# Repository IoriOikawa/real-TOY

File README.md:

# realTOY

> Hardware Implementation for the TOY computer from Princeton.

## Architecture

## Verification

1. Install [Verilator](https://github.com/verilator/verilator), the fastest Verilog/SystemVerilog simulator:

   ```bash
   sudo pacman -S verilator
   ```

1. Install JDK, version doesn't matter that much:

   ```bash
   sudo pacman -S jdk-openjdk
   ```

1. Run all test cases:

   ```bash
   make test
   ```

## Hardware Implementation

TODO

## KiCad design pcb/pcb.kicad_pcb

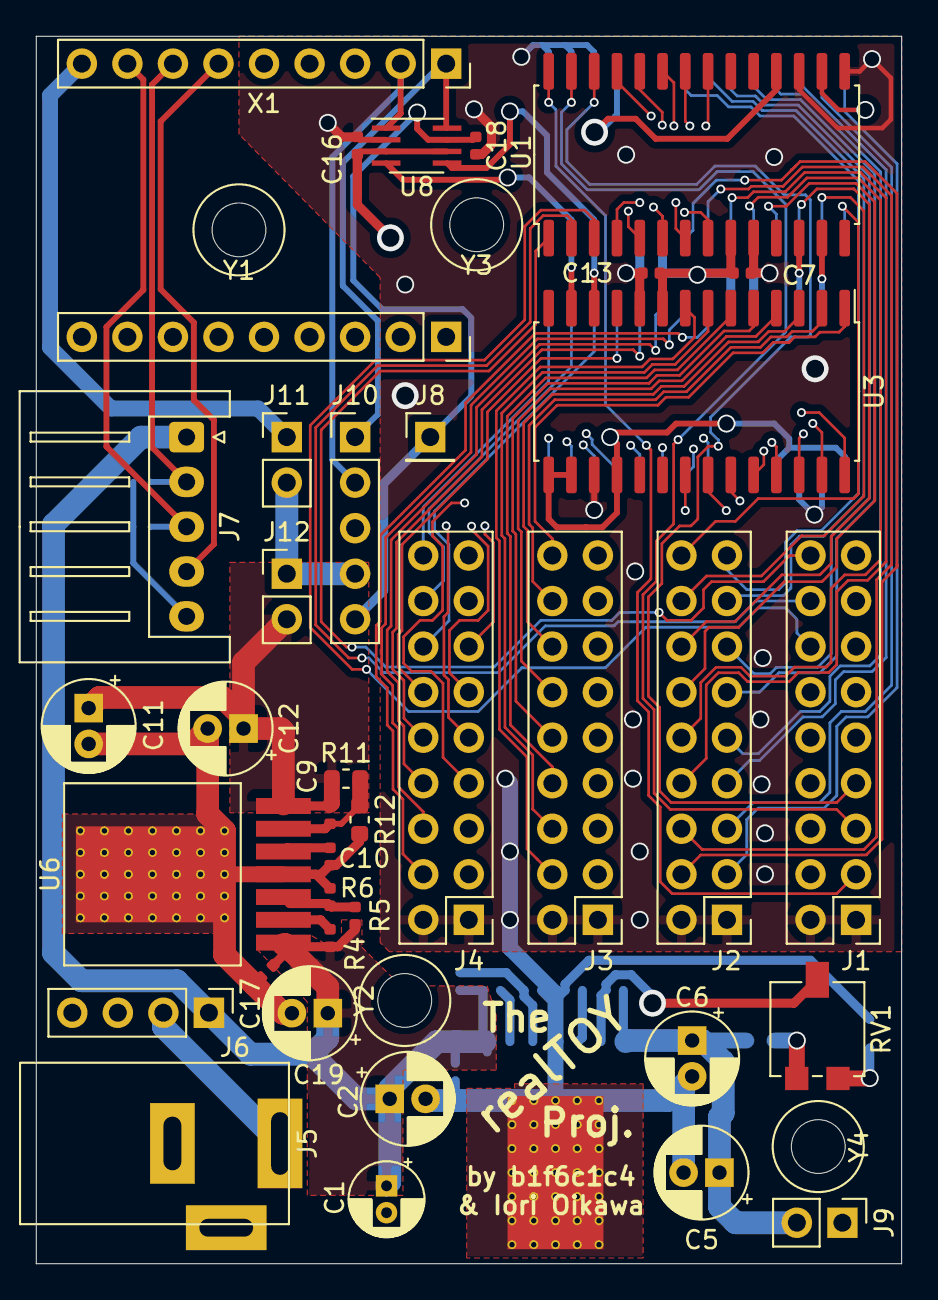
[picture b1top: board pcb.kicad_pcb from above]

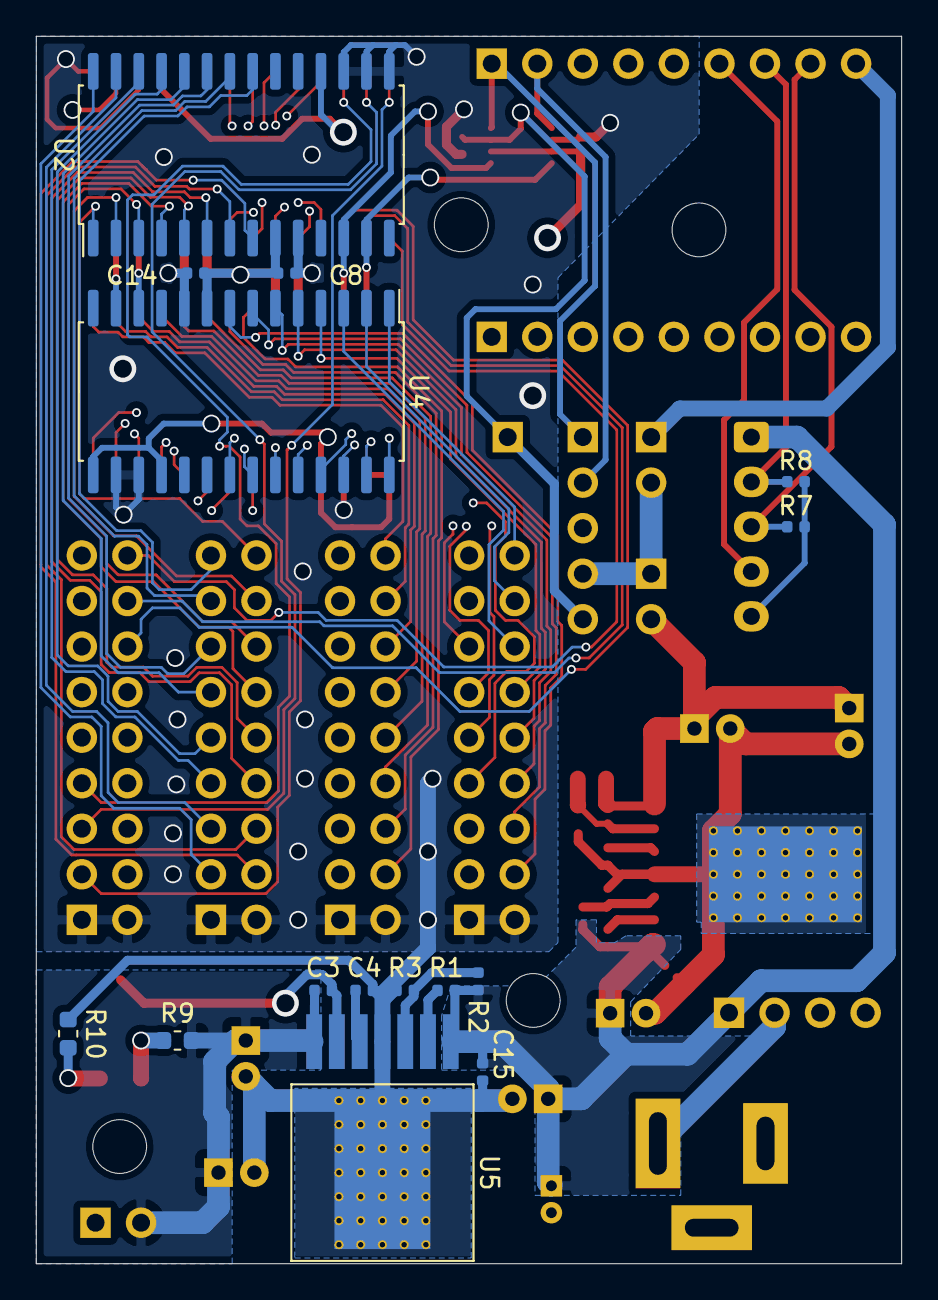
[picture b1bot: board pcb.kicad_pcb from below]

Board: 4 copper layers, 48.3 x 68.5 mm, 56 parts (15 on the bottom side), 90 nets.

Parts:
C1: 22u; CP_Radial_D4.0mm_P1.50mm
C2, C6, C12, C19: 1u; CP_Radial_D5.0mm_P2.00mm
C3, C4, C9, C10: 22n; C_0402_1005Metric
C5, C11: 100u; CP_Radial_D5.0mm_P2.00mm
C7, C8, C13, C14, C15, C16, C17, C18: 100n; C_0402_1005Metric
J1, J2, J3, J4: Conn_02x09_Odd_Even; PinHeader_2x09_P2.54mm_Vertical
J5: Jack-DC; KLDX-0202
J6: Conn_01x04; PinHeader_1x04_P2.54mm_Vertical
J7: Conn_01x05; JST_XH_S5B-XH-A_1x05_P2.50mm_Horizontal
J8: Conn_01x01; PinHeader_1x01_P2.54mm_Vertical
J9, J11, J12: Conn_01x02; PinHeader_1x02_P2.54mm_Vertical
J10: Conn_01x05; PinHeader_1x05_P2.54mm_Vertical
R1, R2, R4, R5, R7, R8: 33k; R_0402_1005Metric
R3, R6: 12k; R_0402_1005Metric
R9: 2.15k, 0.5%; R_0603_1608Metric
R10, R12: 1.02k, 0.5%; R_0603_1608Metric
R11: 5.36k, 0.5%; R_0603_1608Metric
RV1: 1k; Potentiometer_Vishay_TS53YL_Vertical
U1, U2, U3, U4: MCP23017; SOIC-28W_7.5x17.9mm_P1.27mm
U5, U6: LMZ12002
U8: TXS0102; TI-R-PDSO-G8
X1: PLTWS7; PLTWS7_half
Y1, Y2, Y3, Y4: Mount; Hole

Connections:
/+3V3: C18.1, J8.1, J10.5, U8.7
/+5V: J10.4, J11.2, J12.1
/VADJ1: C3.1, C5.1, C6.1, J9.2, R9.1, U5.7
/VADJ2: C9.1, C11.1, C12.1, J12.2, R11.1, U6.7
/VIN: C1.1, C2.1, C15.1, C17.1, C19.1, J6.1, J7.1, R1.1, R2.1, R4.1, R5.1, U5.1, U6.1
/VIN0: J5.1, J6.2
/VU: J11.1, X1.24
/dtr_3v3: J7.2, R8.1, X1.22
/f2p_3v3: J7.4, X1.21
/p2f_3v3: J7.3, R7.1, X1.23
/scl: U1.12, U2.12, U3.12, U4.12, U8.5
/scl_3v3: J10.1, U8.8, X1.16
/sda: U1.13, U2.13, U3.13, U4.13, U8.4
/sda_3v3: J10.2, U8.1, X1.17
GND: C1.2, C2.2, C4.2, C5.2, C6.2, C7.2, C8.2, C10.2, C11.2, C12.2, C13.2, C14.2, C15.2, C16.2, C17.2, C18.2, C19.2, J1.1, J1.2, J2.1, J2.2, J3.1, J3.2, J4.1, J4.2, J5.2, J6.4, J7.5, J10.3, R3.2, R6.2, R7.2, R8.2, R10.2, R12.2, U1.10, U1.15, U1.17, U2.10, U2.15, U2.16, U2.17, U3.10, U3.17, U4.10, U4.16, U4.17, U5.4, U6.4, U8.2, X1.25
unnamed: C3.2, RV1.2, U5.6
unnamed: C4.1, U5.5
unnamed: C9.2, R11.2, R12.1, U6.6
unnamed: C10.1, U6.5
unnamed: J1.3, U1.28
unnamed: J1.4, U1.8
unnamed: J1.5, U1.27
unnamed: J1.6, U1.7
unnamed: J1.7, U1.26
unnamed: J1.8, U1.6
unnamed: J1.9, U1.25
unnamed: J1.10, U1.5
unnamed: J1.11, U1.24
unnamed: J1.12, U1.4
unnamed: J1.13, U1.23
unnamed: J1.14, U1.3
unnamed: J1.15, U1.22
unnamed: J1.16, U1.2
unnamed: J1.17, U1.21
unnamed: J1.18, U1.1
unnamed: J2.3, U2.28
unnamed: J2.4, U2.8
unnamed: J2.5, U2.27
unnamed: J2.6, U2.7
unnamed: J2.7, U2.26
unnamed: J2.8, U2.6
unnamed: J2.9, U2.25
unnamed: J2.10, U2.5
unnamed: J2.11, U2.24
unnamed: J2.12, U2.4
unnamed: J2.13, U2.23
unnamed: J2.14, U2.3
unnamed: J2.15, U2.22
unnamed: J2.16, U2.2
unnamed: J2.17, U2.21
unnamed: J2.18, U2.1
unnamed: J3.3, U3.28
unnamed: J3.4, U3.8
unnamed: J3.5, U3.27
unnamed: J3.6, U3.7
unnamed: J3.7, U3.26
unnamed: J3.8, U3.6
unnamed: J3.9, U3.25
unnamed: J3.10, U3.5
unnamed: J3.11, U3.24
unnamed: J3.12, U3.4
unnamed: J3.13, U3.23
unnamed: J3.14, U3.3
unnamed: J3.15, U3.22
unnamed: J3.16, U3.2
unnamed: J3.17, U3.21
unnamed: J3.18, U3.1
unnamed: J4.3, U4.28
unnamed: J4.4, U4.8
unnamed: J4.5, U4.27
unnamed: J4.6, U4.7
unnamed: J4.7, U4.26
unnamed: J4.8, U4.6
unnamed: J4.9, U4.25
unnamed: J4.10, U4.5
unnamed: J4.11, U4.24
unnamed: J4.12, U4.4
unnamed: J4.13, U4.23
unnamed: J4.14, U4.3
unnamed: J4.15, U4.22
unnamed: J4.16, U4.2
unnamed: J4.17, U4.21
unnamed: J4.18, U4.1
unnamed: R1.2, U5.2
unnamed: R2.2, R3.1, U5.3
unnamed: R4.2, U6.2
unnamed: R5.2, R6.1, U6.3
unnamed: R9.2, RV1.3
unnamed: R10.1, RV1.1
VDD: C7.1, C8.1, C13.1, C14.1, C16.1, J6.3, J9.1, U1.9, U1.16, U1.18, U2.9, U2.18, U3.9, U3.15, U3.16, U3.18, U4.9, U4.15, U4.18, U8.3, U8.6

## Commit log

2020-09-11 WIP: framework
2020-09-11 no explicit
2020-09-11 many stuff
2020-09-11 decoder
2020-09-11 dpath
2020-09-11 system
2020-09-11 WIP: verilator
2020-09-11 split
2020-09-11 fix bugs
2020-09-11 fix more bugs
2020-09-11 WIP: verilator fix bugs
2020-09-12 WIP: fix logic
2020-09-12 bug fixed
2020-09-12 small bugs
2020-09-12 self-modify
2020-09-12 Add TOY virtual machine code in Java
    The code is downloaded from the following web page:
    https://introcs.cs.princeton.edu/java/64simulator/
2020-09-12 WIP: test
2020-09-12 add gitattributes
2020-09-17 add dxf
2020-09-19 better front
2020-09-21 fix tiny problems
2020-09-21 fix interface syntax
2020-09-21 fix warnings
2020-09-25 WIP: i2c
2020-09-26 fix i2c
2020-09-26 uart
2020-09-26 top lvl
2020-09-26 adjustments
2020-09-26 scripts
2020-09-26 pull down
2020-09-28 pcb adjust
2020-09-28 no in1 routing
2020-09-28 many pcb changes
2020-09-28 tune
2020-10-02 i2c comments
2020-11-08 change design to fit pcb
2020-11-08 fix oci
2020-11-08 verilator
2020-11-08 fix things
2020-11-08 flash
